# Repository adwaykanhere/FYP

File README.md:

# FYP
Final Year Project: EEG acquisition circuit and Error related correction using deep learning

Software:
We are implementing the model published in the paper --> https://arxiv.org/pdf/1611.08024.pdf

The data is downloaded from kaggle and can be found here --> https://www.kaggle.com/c/inria-bci-challenge

## More updates soon!

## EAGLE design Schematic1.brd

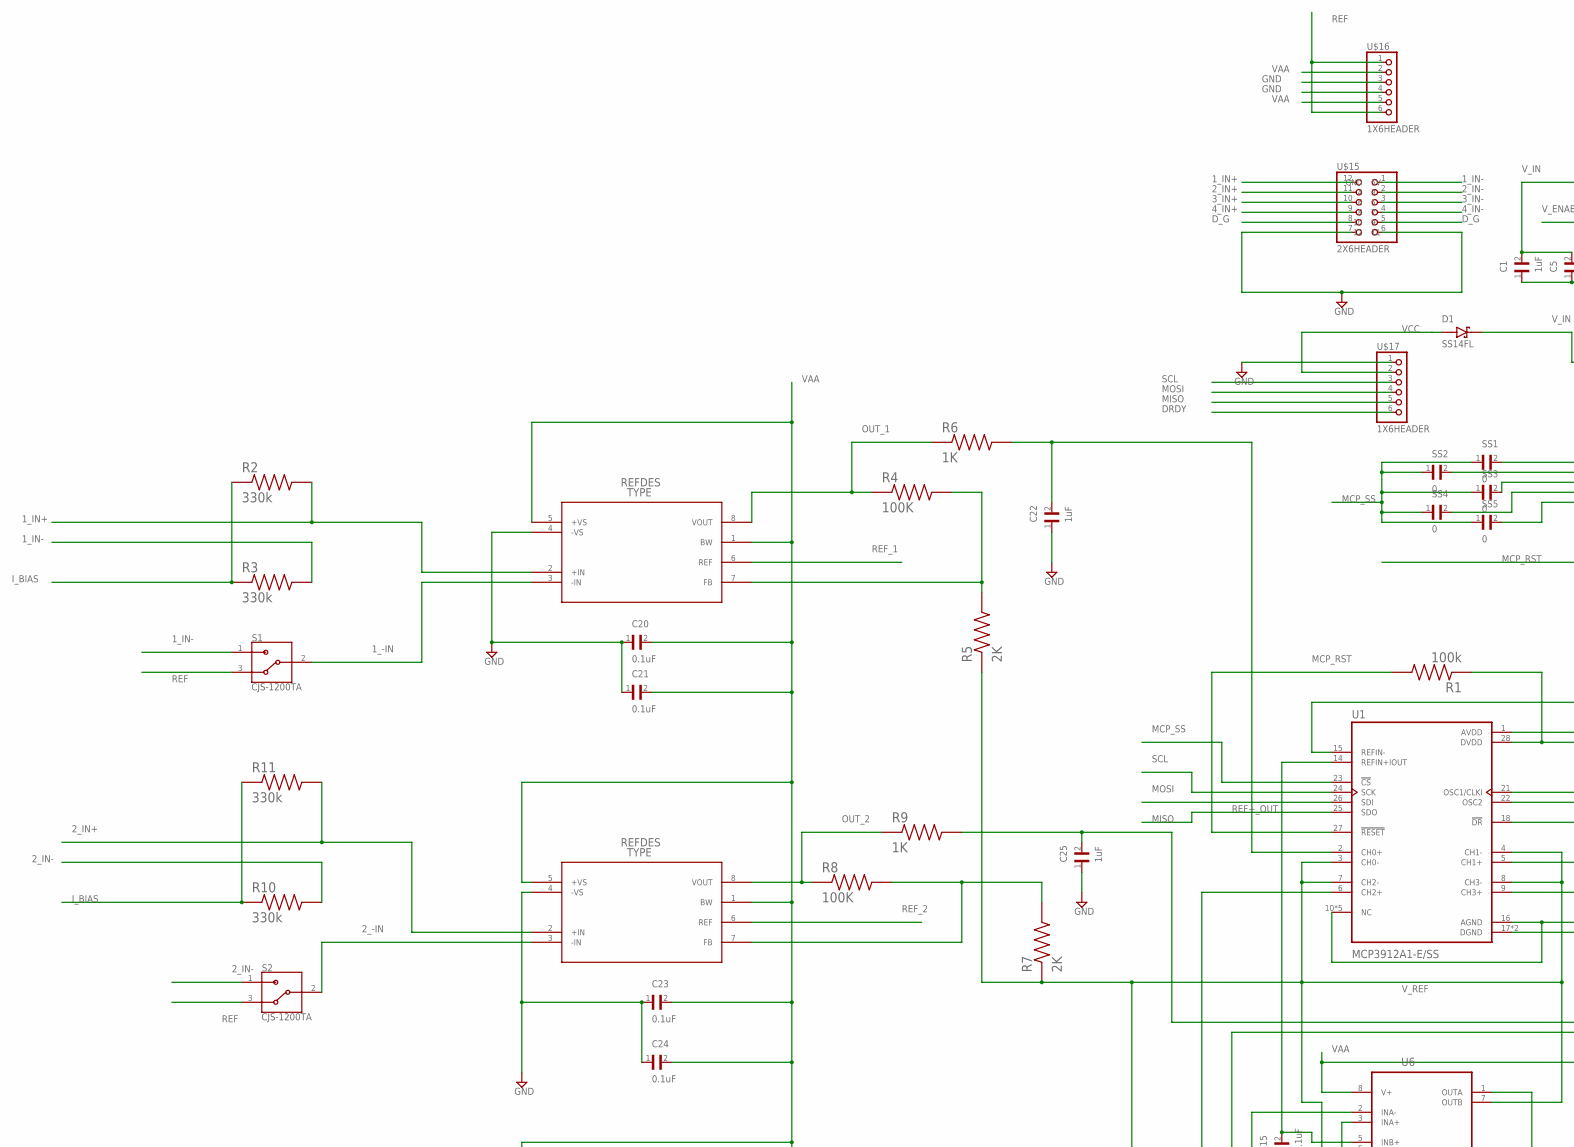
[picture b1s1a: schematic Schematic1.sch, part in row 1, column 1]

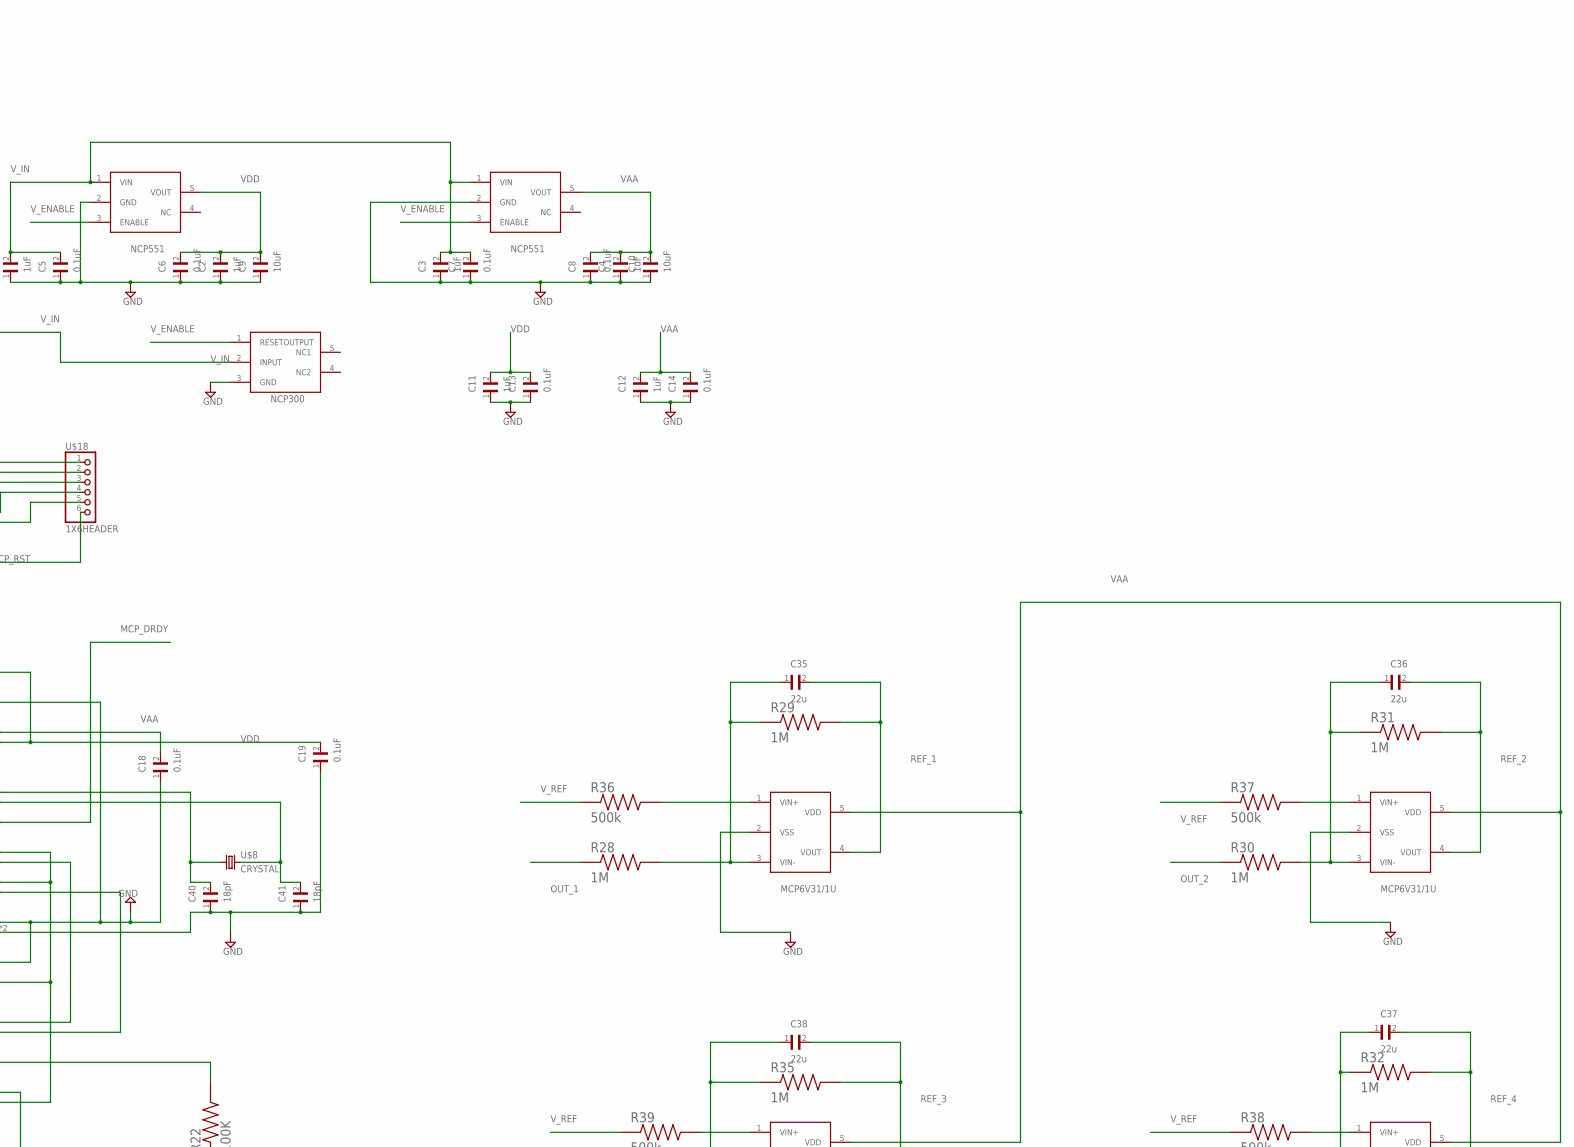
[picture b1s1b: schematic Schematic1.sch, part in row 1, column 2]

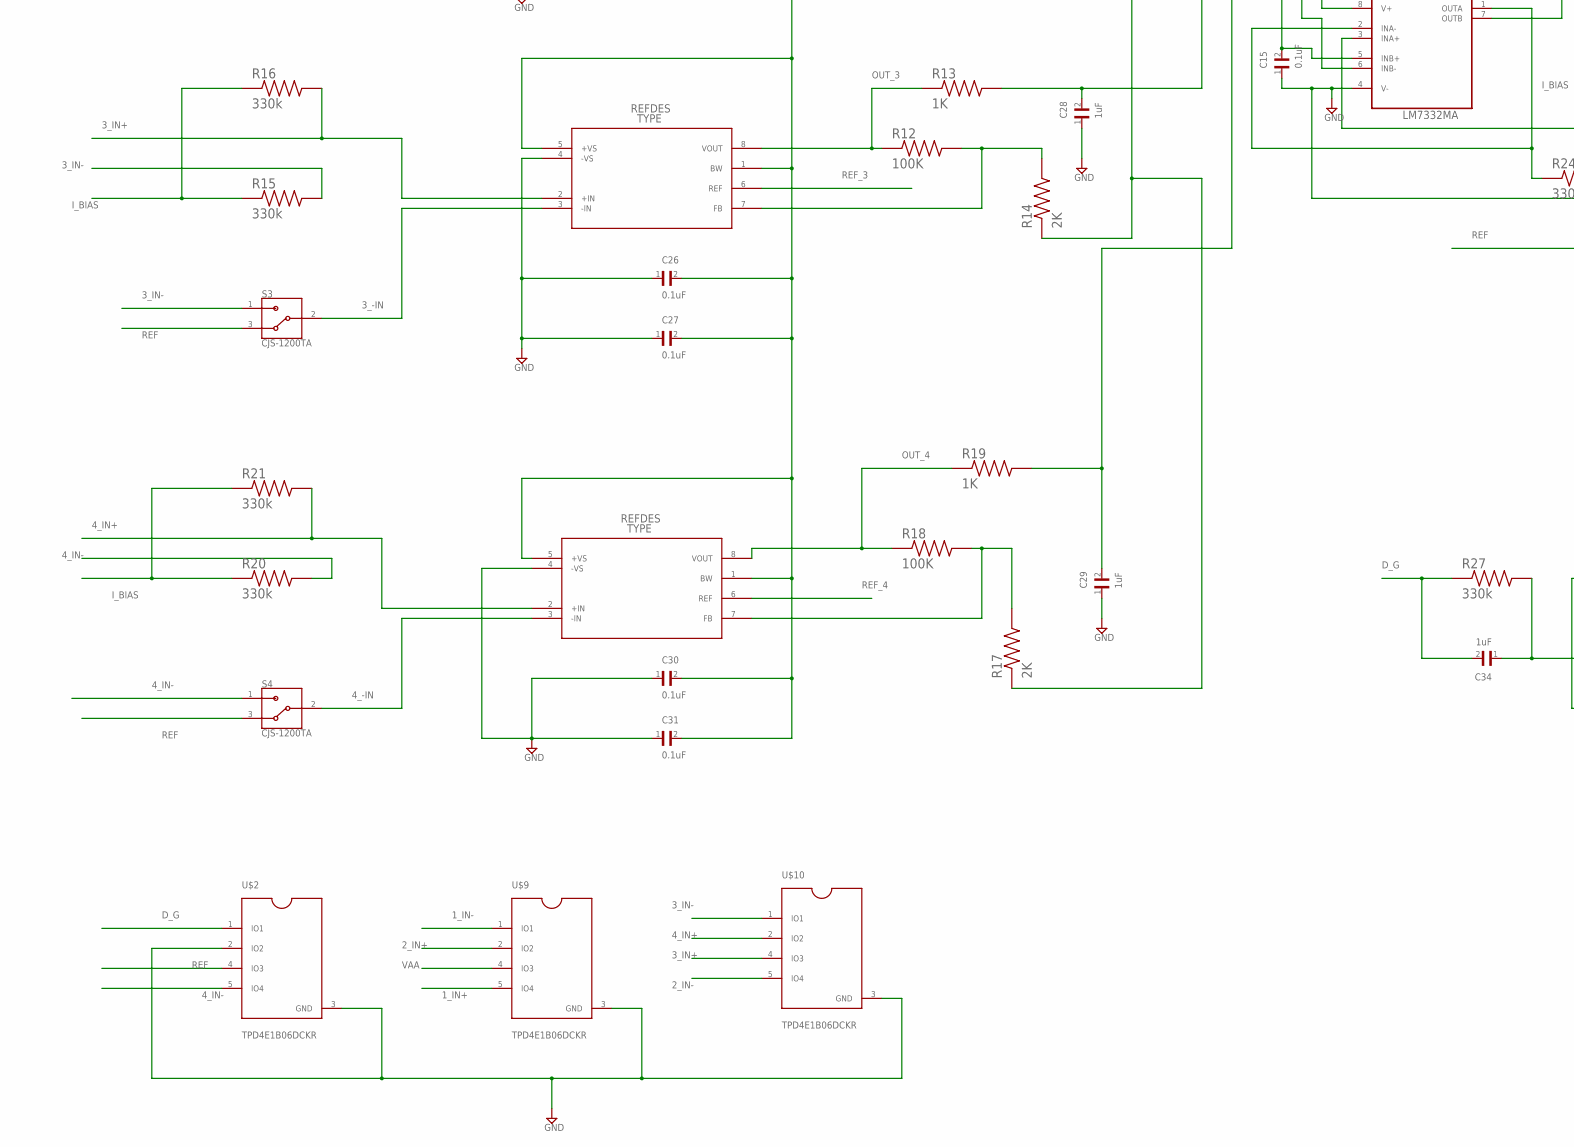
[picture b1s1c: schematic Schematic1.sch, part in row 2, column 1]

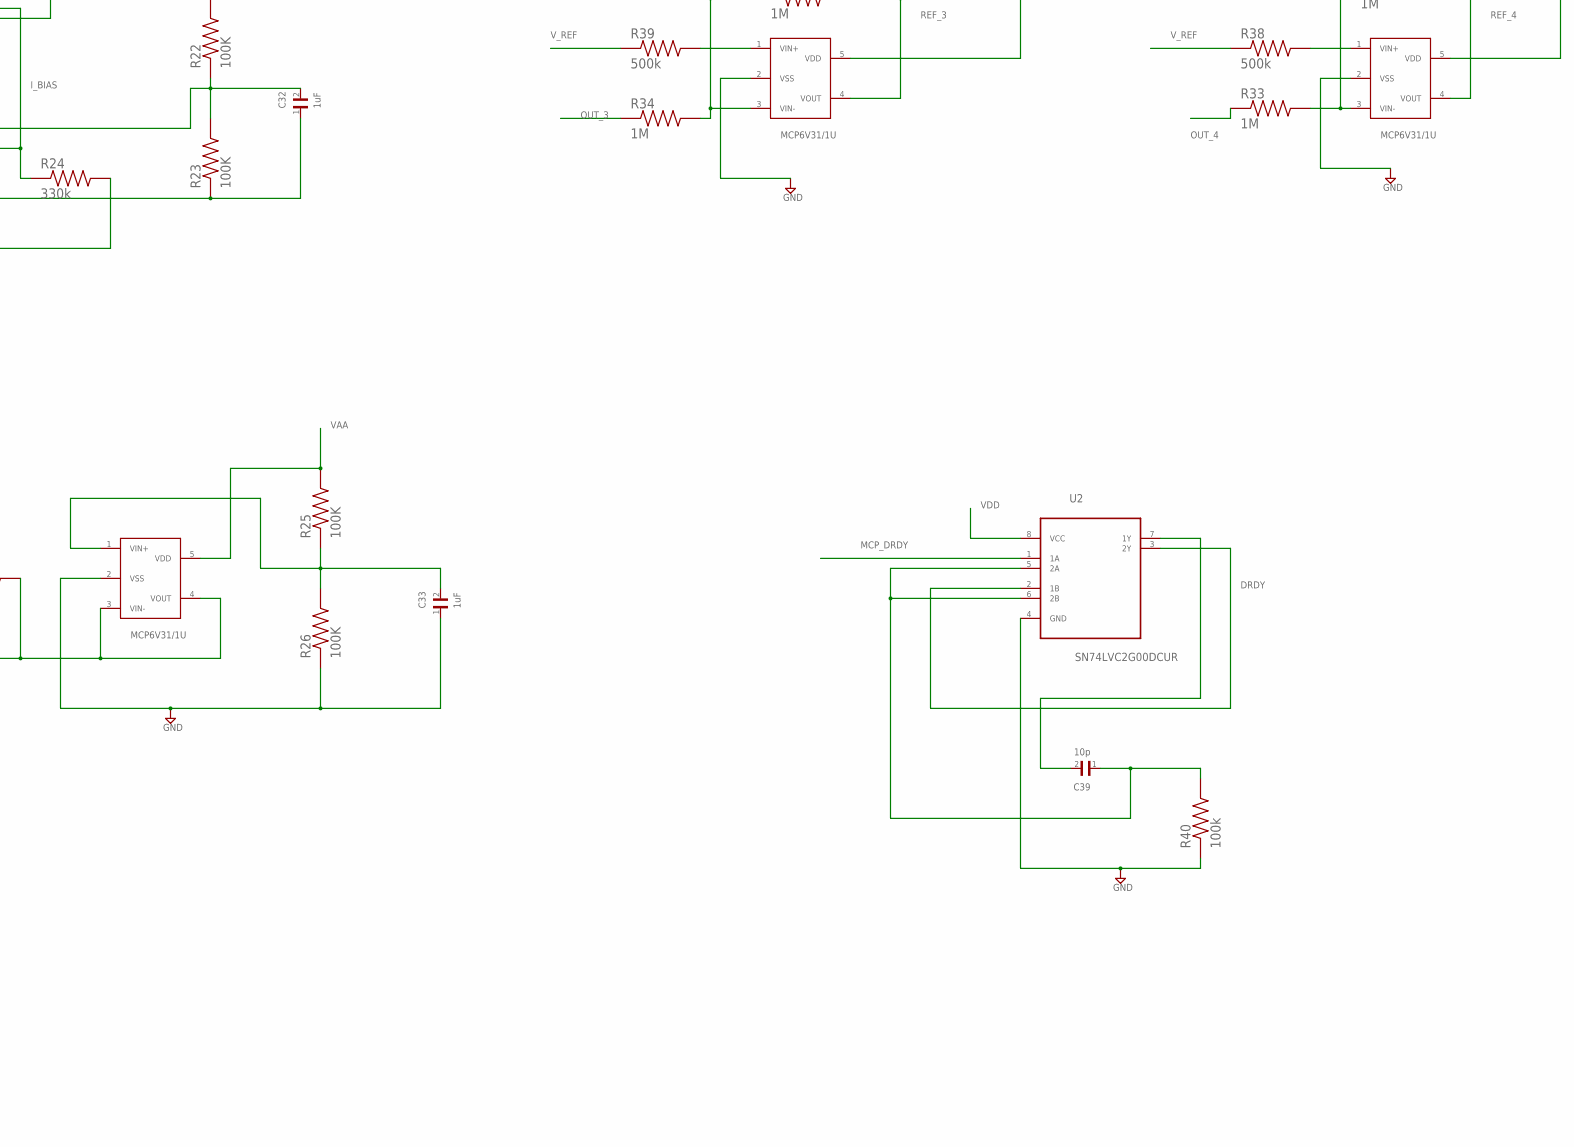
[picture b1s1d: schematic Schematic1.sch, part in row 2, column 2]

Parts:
AD1, AD2, AD3, AD8237: AD8237ARMZ; RM_8
C1, C2, C3, C4, C11, C12, C22, C25, C28, C29, C32, C33, C34: 1uF; CAPC3216X180N
C5, C6, C7, C8, C13, C14, C15, C18, C19, C20, C21, C23, C24, C26, C27, C30, C31: 0.1uF; CAPC3216X180N
C9, C10: 10uF; CAPC3216X180N
C35, C36, C37, C38: 22u; CAPC1608X100N
C39: 10p; CAPC1608X90N
C40, C41: 18pF; CAPC1608X100N
D1: SS14FL; SODFL3617X108N
R1, R40: 100k; RESC1608X55N
R2, R3, R10, R11, R15, R16, R20, R21, R24, R27: 330k; RESC1608X55N
R4, R8, R12, R18, R22, R23, R25, R26: 100K; RESC1608X55N
R5, R7, R14, R17: 2K; RESC1608X55N
R6, R9, R13, R19: 1K; RESC1608X55N
R28, R29, R30, R31, R32, R33, R34, R35: 1M; RESC1608X55N
R36, R37, R38, R39: 500k; RESC1608X55N
S1, S2, S3, S4: CJS-1200TA; SW_CJS-1200TA
SS1, SS2, SS3, SS4, SS5: 0; CAPC0603X33N
U1: MCP3912A1-E/SS; SOP65P780X200-28N
U2: SN74LVC2G00DCUR; SOP50P310X90-8N
U6: LM7332MA; SOIC127P600X175-8N
U$1, U$4: NCP551; TSOP-5
U$2, U$9, U$10: TPD4E1B06DCKR; SC70-6
U$3, U$11, U$12, U$13, U$14: MCP6V31/1U; SOT23-5
U$5: NCP300; SOT23-5
U$8: CRYSTAL
U$15: 2X6HEADER; PINHEADER2X6
U$16, U$17, U$18: 1X6HEADER; PINHEADER1X6

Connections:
1_-IN: AD8237.3 (-IN), S1.2
1_IN+: AD8237.2 (+IN), R2.2, U$9.5 (IO4), U$15.12 (5V)
1_IN-: R3.2, S1.1, U$9.1 (IO1), U$15.1 (GND)
2_-IN: AD1.3 (-IN), S2.2
2_IN+: AD1.2 (+IN), R11.2, U$9.2 (IO2), U$15.11 (3)
2_IN-: R10.2, S2.1, U$10.5 (IO4), U$15.2 (4)
3_-IN: AD2.3 (-IN), S3.2
3_IN+: AD2.2 (+IN), R16.2, U$10.4 (IO3), U$15.10 (5)
3_IN-: R15.2, S3.1, U$10.1 (IO1), U$15.3 (6)
4_-IN: AD3.3 (-IN), S4.2
4_IN+: AD3.2 (+IN), R21.2, U$10.2 (IO2), U$15.9 (7)
4_IN-: R20.2, S4.1, U$2.5 (IO4), U$15.4 (8)
DRDY: U2.2 (1B), U2.3 (2Y), U$17.6
D_G: C34.2, R27.1, U$2.1 (IO1), U$15.5 (10), U$15.8 (9)
GND: AD1.4 (-VS), AD2.4 (-VS), AD3.4 (-VS), AD8237.4 (-VS), C1.1, C2.1, C3.1, C4.1, C5.1, C6.1, C7.1, C8.1, C9.1, C10.1, C11.1, C12.1, C13.1, C14.1, C15.1, C18.1, C19.1, C20.1, C21.1, C22.1, C23.1, C24.1, C25.1, C26.1, C27.1, C28.1, C29.1, C30.1, C31.1, C32.1, C33.1, C40.1, C41.1, R23.1, R26.1, R40.1, U1.10 (NC), U1.11 (NC), U1.12 (NC), U1.13 (NC), U1.15 (REFIN-), U1.16 (AGND), U1.17 (DGND), U1.19 (NC), U1.20 (DGND), U2.4 (GND), U6.4 (V-), U$1.2 (GND), U$2.2 (IO2), U$2.3 (GND), U$3.2 (VSS), U$4.2 (GND), U$5.3 (GND), U$9.3 (GND), U$10.3 (GND), U$11.2 (VSS), U$12.2 (VSS), U$13.2 (VSS), U$14.2 (VSS), U$15.6 (12), U$15.7 (11), U$16.3, U$16.4, U$17.1
I_BIAS: R2.1, R3.1, R10.1, R11.1, R15.1, R16.1, R20.1, R21.1, R24.1, U6.1 (OUTA), U6.2 (INA-)
MCP_DRDY: U1.18 (!DR), U2.1 (1A)
MCP_RST: R1.2, U1.27 (!RESET), U$18.6
MCP_SS: SS1.1, SS2.1, SS3.1, SS4.1, SS5.1, U1.23 (!CS)
MISO: U1.25 (SDO), U$17.5
MOSI: U1.26 (SDI), U$17.4
unnamed: C41.2, U1.22 (OSC2), U$8.2
unnamed: C40.2, U1.21 (OSC1/CLKI), U$8.1
unnamed: SS2.2, U$18.2
unnamed: C29.2, R19.2, U1.9 (CH3+)
unnamed: AD8237.7 (FB), R4.2, R5.2
unnamed: AD2.7 (FB), R12.2, R14.2
unnamed: C22.2, R6.2, U1.2 (CH0+)
unnamed: AD1.7 (FB), R7.2, R8.2
unnamed: C25.2, R9.2, U1.5 (CH1+)
unnamed: C28.2, R13.2, U1.6 (CH2+)
unnamed: AD3.7 (FB), R17.2, R18.2
unnamed: C32.2, R22.1, R23.2, U6.3 (INA+)
unnamed: C33.2, R25.1, R26.2, U$3.1 (VIN+)
unnamed: C34.1, R27.2, U$3.3 (VIN-), U$3.4 (VOUT)
unnamed: C38.1, R34.2, R35.1, U$13.3 (VIN-)
unnamed: SS1.2, U$18.1
unnamed: C37.1, R32.1, R33.2, U$14.3 (VIN-)
unnamed: SS3.2, U$18.3
unnamed: R36.2, U$11.1 (VIN+)
unnamed: C39.1, R40.2, U2.5 (2A), U2.6 (2B)
unnamed: C39.2, U2.7 (1Y)
unnamed: R39.2, U$13.1 (VIN+)
unnamed: SS4.2, U$18.4
unnamed: R38.2, U$14.1 (VIN+)
unnamed: C36.1, R30.2, R31.1, U$12.3 (VIN-)
unnamed: R37.2, U$12.1 (VIN+)
unnamed: SS5.2, U$18.5
unnamed: C35.1, R28.2, R29.1, U$11.3 (VIN-)
OUT_1: AD8237.8 (VOUT), R4.1, R6.1, R28.1
OUT_2: AD1.8 (VOUT), R8.1, R9.1, R30.1
OUT_3: AD2.8 (VOUT), R12.1, R13.1, R34.1
OUT_4: AD3.8 (VOUT), R18.1, R19.1, R33.1
REF: R24.2, S1.3, S2.3, S3.3, S4.3, U$2.4 (IO3), U$16.1, U$16.6
REF+_OUT: C15.2, U1.14 (REFIN+IOUT), U6.5 (INB+)
REF_1: AD8237.6 (REF), C35.2, R29.2, U$11.4 (VOUT)
REF_2: AD1.6 (REF), C36.2, R31.2, U$12.4 (VOUT)
REF_3: AD2.6 (REF), C38.2, R35.2, U$13.4 (VOUT)
REF_4: AD3.6 (REF), C37.2, R32.2, U$14.4 (VOUT)
SCL: U1.24 (SCK), U$17.3
VAA: AD1.1 (BW), AD1.5 (+VS), AD2.1 (BW), AD2.5 (+VS), AD3.1 (BW), AD3.5 (+VS), AD8237.1 (BW), AD8237.5 (+VS), C4.2, C8.2, C10.2, C12.2, C14.2, C18.2, C20.2, C21.2, C23.2, C24.2, C26.2, C27.2, C30.2, C31.2, R22.2, R25.2, U1.1 (AVDD), U6.8 (V+), U$3.5 (VDD), U$4.5 (VOUT), U$9.4 (IO3), U$11.5 (VDD), U$12.5 (VDD), U$13.5 (VDD), U$14.5 (VDD), U$16.2, U$16.5
VCC: D1.A, U$17.2
VDD: C2.2, C6.2, C9.2, C11.2, C13.2, C19.2, R1.1, U1.28 (DVDD), U2.8 (VCC), U$1.5 (VOUT)
V_ENABLE: U$1.3 (ENABLE), U$4.3 (ENABLE), U$5.1 (RESETOUTPUT)
V_IN: C1.2, C3.2, C5.2, C7.2, D1.C (K), U$1.1 (VIN), U$4.1 (VIN), U$5.2 (INPUT)
V_REF: R5.1, R7.1, R14.1, R17.1, R36.1, R37.1, R38.1, R39.1, U1.3 (CH0-), U1.4 (CH1-), U1.7 (CH2-), U1.8 (CH3-), U6.6 (INB-), U6.7 (OUTB)

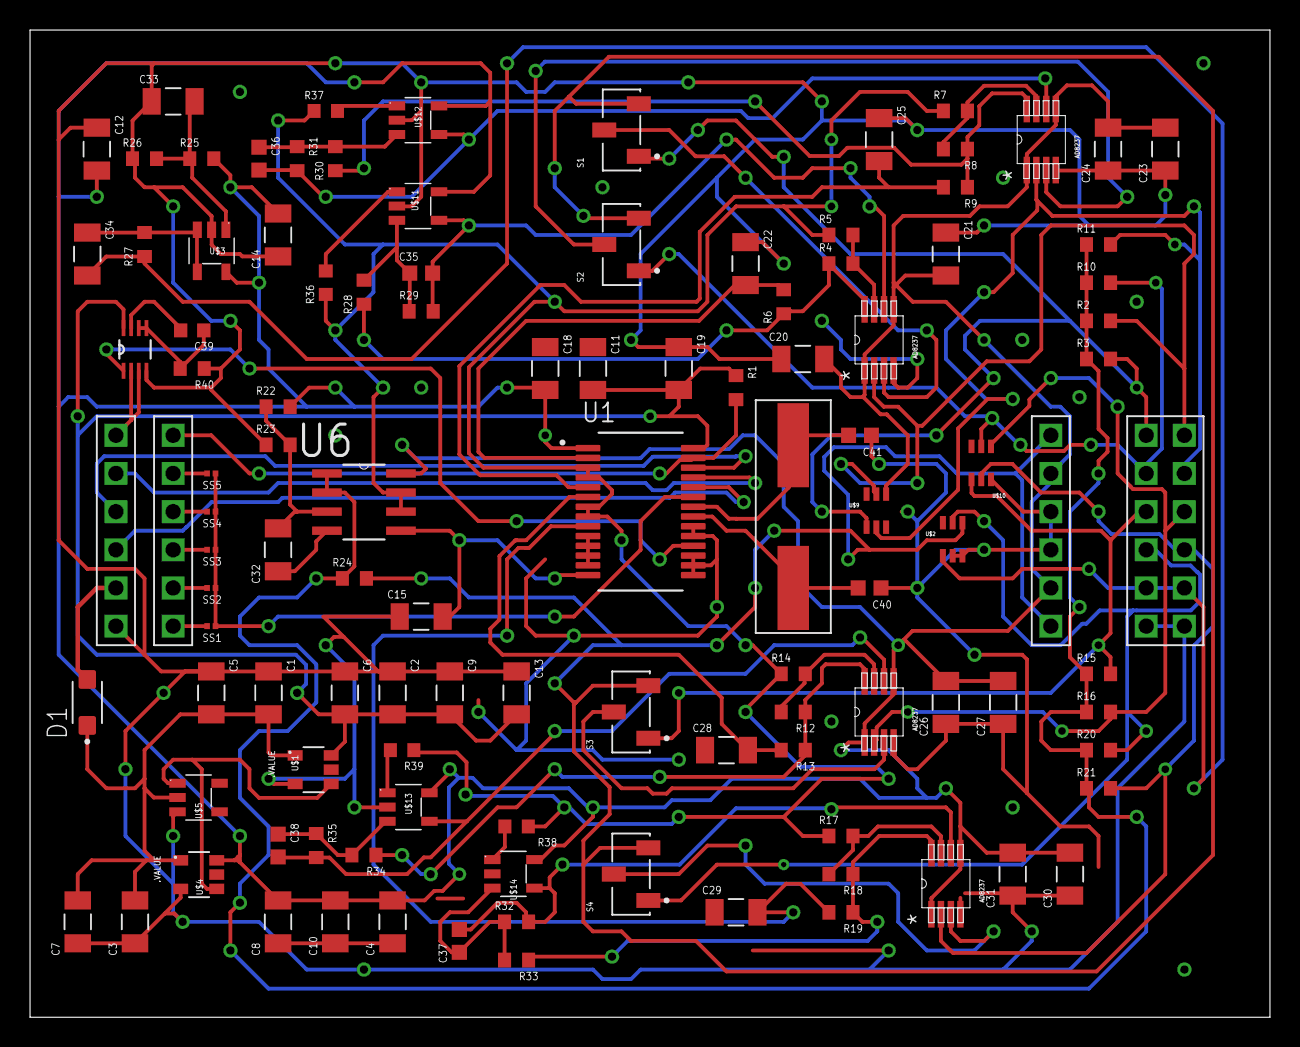
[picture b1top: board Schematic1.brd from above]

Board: 2 copper layers, 82.5 x 65.7 mm, 112 parts (0 on the bottom side), 66 nets.

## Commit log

2020-05-16 Create filtering.py
    Basic filetring steps using MNE
2020-05-17 change in samp_freq
2020-06-14 Create BCI_DL_V5.ipynb
    Main processing file
2020-06-27 Create BCI_DL_V6.ipynb
    Final script
2020-07-03 Hardware files uploaded
